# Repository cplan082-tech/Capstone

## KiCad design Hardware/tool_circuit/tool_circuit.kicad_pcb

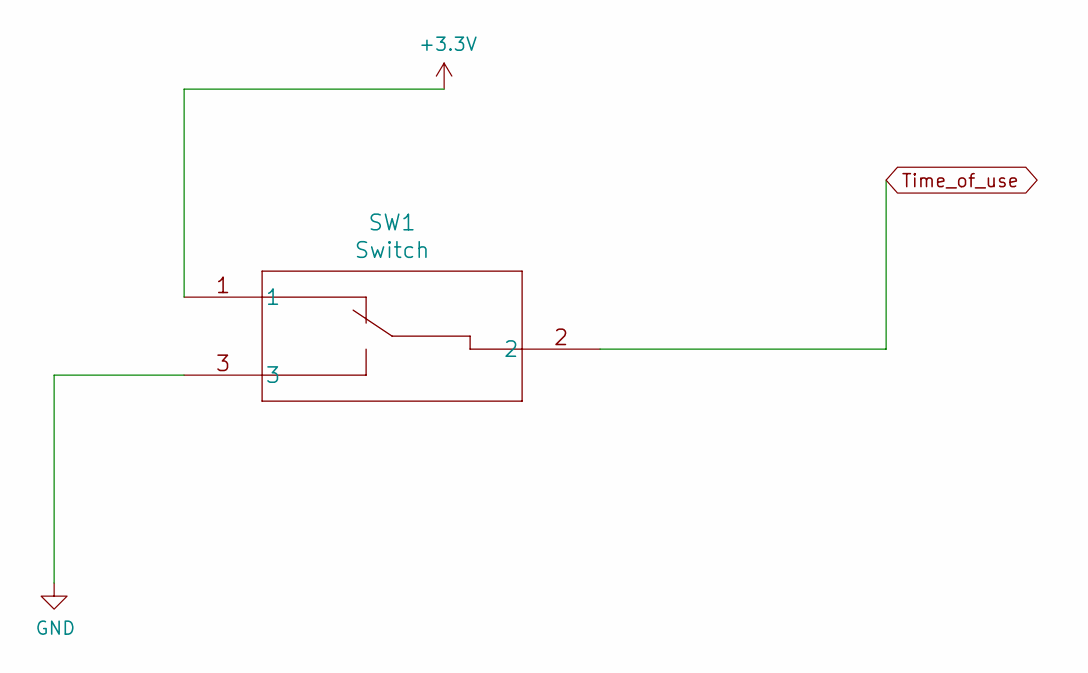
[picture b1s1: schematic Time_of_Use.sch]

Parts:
SW1: Switch; 1825255-1

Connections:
+3V3: SW1.1; also elsewhere on the board
GND: SW1.3; also elsewhere on the board
Time_of_use: SW1.2; also elsewhere on the board

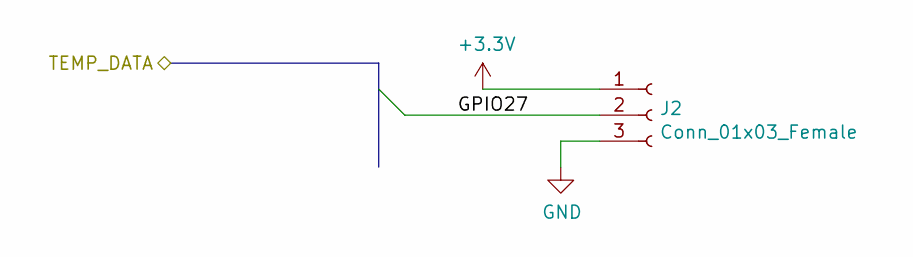
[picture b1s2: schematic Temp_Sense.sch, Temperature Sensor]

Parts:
J2: Conn_01x03_Female; PinHeader_1x03_P2.54mm_Vertical

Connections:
+3V3: J2.1; also elsewhere on the board
GND: J2.3; also elsewhere on the board
GPIO27_GEN2: J2.2; also elsewhere on the board

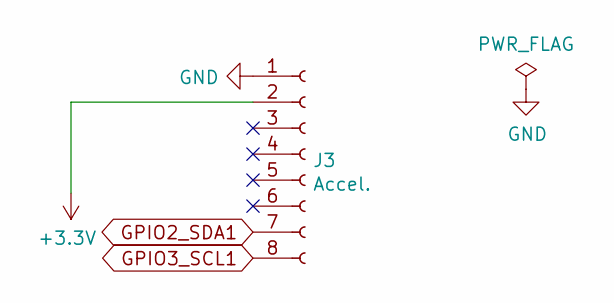
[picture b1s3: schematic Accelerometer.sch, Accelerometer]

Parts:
J3: Accel.; PinHeader_1x08_P2.54mm_Vertical

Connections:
+3V3: J3.2; also elsewhere on the board
GND: J3.1; also elsewhere on the board
GPIO2_SDA1: J3.7; also elsewhere on the board
GPIO3_SCL1: J3.8; also elsewhere on the board

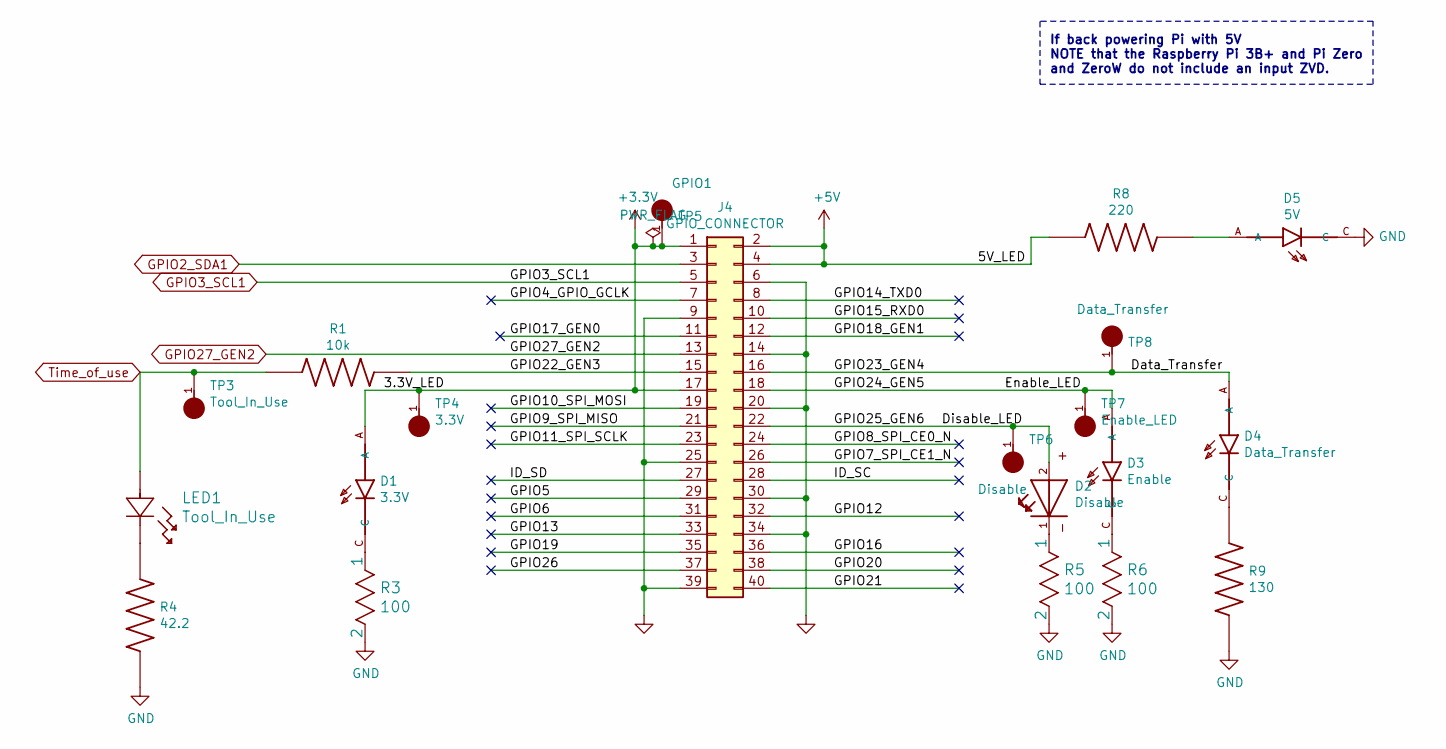
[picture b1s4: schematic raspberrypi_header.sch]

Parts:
D1: 3.3V; LED_WP7113GD
D2: Disable; LED-5MM-ROUND
D3: Enable; LED_WP7113GD
D4: Data_Transfer; LED_WP7113YD
D5: 5V; LED_WP7113GD
J4: GPIO_CONNECTOR; PinSocket_2x20_P2.54mm_Vertical_Centered_Anchor
LED1: Tool_In_Use; 151034BS03000
R1: 10k; RESC3115X60N
R3, R5, R6: 100; RESC3115X60N
R4: 42.2; RESC3116X65N
R8: 220; RESC3216X70N
R9: 130; RESC3116X65N
TP3: Tool_In_Use; HARWIN_S2751-46R
TP4: 3.3V; HARWIN_S2751-46R
TP5: GPIO1; HARWIN_S2751-46R
TP6: Disable; HARWIN_S2751-46R
TP7: Enable_LED; HARWIN_S2751-46R
TP8: Data_Transfer; HARWIN_S2751-46R

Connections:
+3V3: D1.A, J4.1, J4.17, TP4.1, TP5.1; also elsewhere on the board
+5V: J4.2, J4.4, R8.1; also elsewhere on the board
/raspberrypi_header.sch/Data_Transfer: D4.A, J4.16, TP8.1
/raspberrypi_header.sch/Disable_LED: D2.2, J4.22, TP6.1
/raspberrypi_header.sch/Enable_LED: D3.A, J4.18, TP7.1
/raspberrypi_header.sch/GPIO4_GPIO_GCLK: J4.7
/raspberrypi_header.sch/GPIO5: J4.29
/raspberrypi_header.sch/GPIO6: J4.31
/raspberrypi_header.sch/GPIO7_SPI_CE1_N: J4.26
/raspberrypi_header.sch/GPIO8_SPI_CE0_N: J4.24
/raspberrypi_header.sch/GPIO9_SPI_MISO: J4.21
/raspberrypi_header.sch/GPIO10_SPI_MOSI: J4.19
/raspberrypi_header.sch/GPIO11_SPI_SCLK: J4.23
/raspberrypi_header.sch/GPIO12: J4.32
/raspberrypi_header.sch/GPIO13: J4.33
/raspberrypi_header.sch/GPIO14_TXD0: J4.8
/raspberrypi_header.sch/GPIO15_RXD0: J4.10
/raspberrypi_header.sch/GPIO16: J4.36
/raspberrypi_header.sch/GPIO17_GEN0: J4.11
/raspberrypi_header.sch/GPIO18_GEN1: J4.12
/raspberrypi_header.sch/GPIO19: J4.35
/raspberrypi_header.sch/GPIO20: J4.38
/raspberrypi_header.sch/GPIO21: J4.40
/raspberrypi_header.sch/GPIO22_GEN3: J4.15, R1.2
/raspberrypi_header.sch/GPIO26: J4.37
/raspberrypi_header.sch/ID_SC: J4.28
/raspberrypi_header.sch/ID_SD: J4.27
GND: D5.C, J4.6, J4.9, J4.14, J4.20, J4.25, J4.30, J4.34, J4.39, R3.2, R4.2, R5.2, R6.2, R9.2; also elsewhere on the board
GPIO2_SDA1: J4.3; also elsewhere on the board
GPIO3_SCL1: J4.5; also elsewhere on the board
GPIO27_GEN2: J4.13; also elsewhere on the board
unnamed: D1.C, R3.1
unnamed: D2.1, R5.1
unnamed: D3.C, R6.1
unnamed: D4.C, R9.1
unnamed: D5.A, R8.2
unnamed: LED1.1, R4.1
Time_of_use: LED1.2, R1.1, TP3.1; also elsewhere on the board

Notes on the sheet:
If back powering Pi with 5V NOTE that the Raspberry Pi 3B+ and Pi Zero and ZeroW do not include an input ZVD.

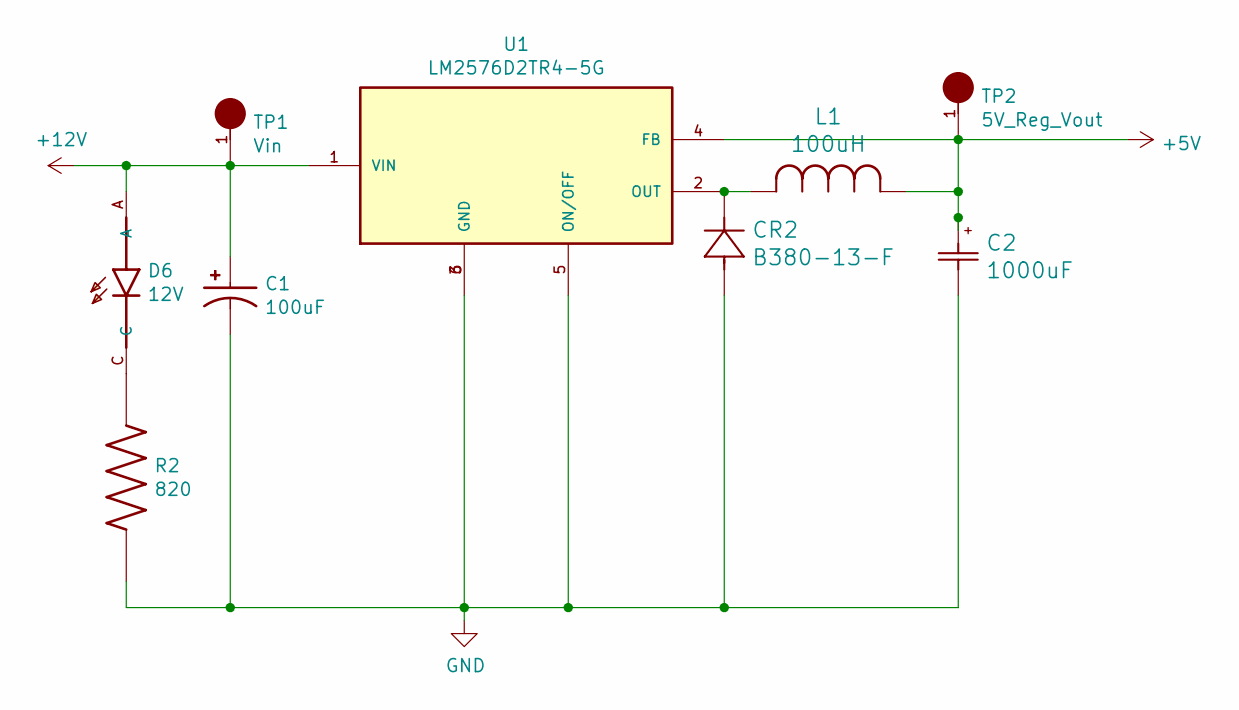
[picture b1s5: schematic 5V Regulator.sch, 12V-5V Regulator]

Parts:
C1: 100uF; CAPPRD500W60D1000H1250; PARTREV 28-FEB-20
C2: 1000uF; URS1E102MHD1TO
CR2: B380-13-F
D6: 12V; LED_WP7113GD
L1: 100uH; IHLP4040DZER101M11
R2: 820; RESC3115X65N
TP1: Vin; HARWIN_S2751-46R
TP2: 5V_Reg_Vout; HARWIN_S2751-46R
U1: LM2576D2TR4-5G; D2PAK-5

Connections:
+5V: C2.1, L1.1, TP2.1, U1.4 (FB); also elsewhere on the board
+12V: C1.P, D6.A, TP1.1, U1.1 (VIN); also elsewhere on the board
GND: C1.N, C2.2, CR2.2, R2.2, U1.3 (GND), U1.5 (ON/OFF), U1.6 (GND); also elsewhere on the board
unnamed: CR2.1, L1.2, U1.2 (OUT)
unnamed: D6.C, R2.1

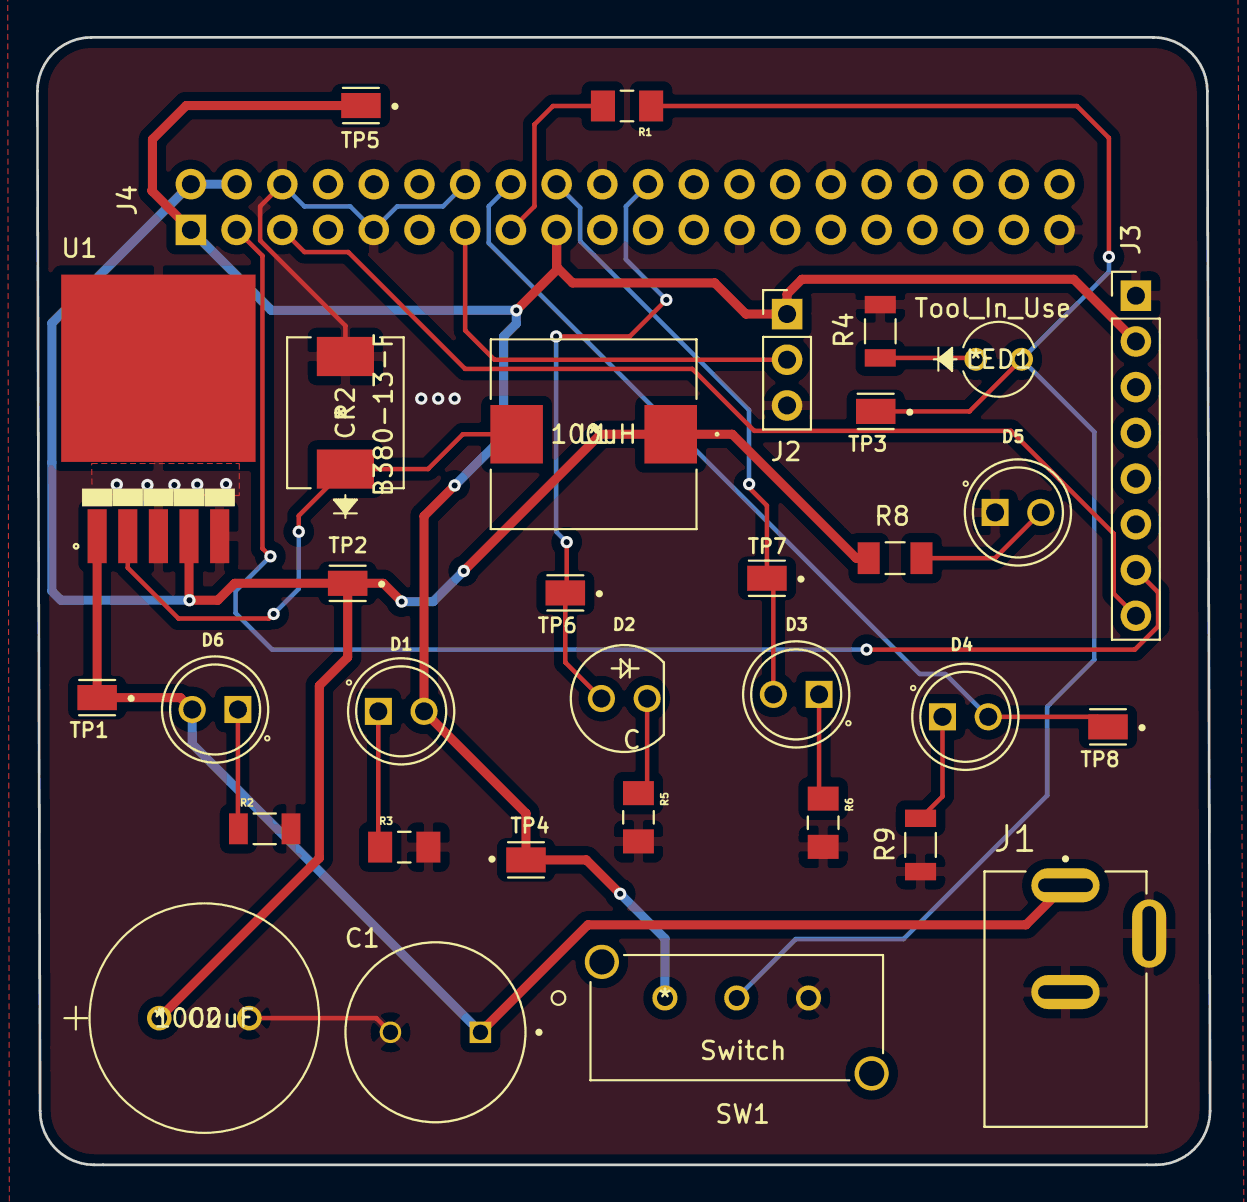
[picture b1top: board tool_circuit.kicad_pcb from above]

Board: 2 copper layers, 65.2 x 62.6 mm, 33 parts (1 on the bottom side), 20 nets.

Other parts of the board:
J1: EJ503A; MPD_EJ503A

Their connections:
+12V: J1.1; also elsewhere on the board
GND: J1.2, J1.3; also elsewhere on the board

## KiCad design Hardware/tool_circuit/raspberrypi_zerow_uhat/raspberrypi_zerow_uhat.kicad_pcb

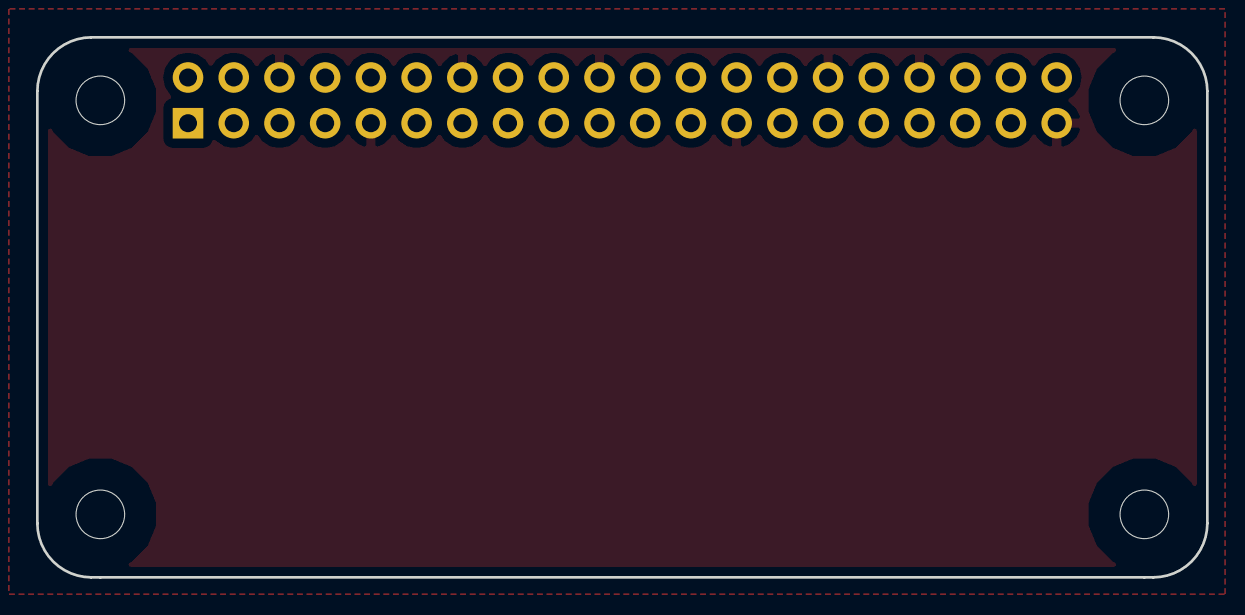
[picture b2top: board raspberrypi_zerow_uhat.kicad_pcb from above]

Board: 2 copper layers, 65.0 x 30.0 mm, 5 parts (1 on the bottom side), 3 nets, no tracks yet.

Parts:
H1, H2, H3, H4: MountingHole; MountingHole_2.7mm_M2.5_uHAT_RPi
J1: GPIO_CONNECTOR; PinSocket_2x20_P2.54mm_Vertical_Centered_Anchor

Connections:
+3V3: J1.1, J1.17
+5V: J1.2, J1.4
GND: J1.6, J1.9, J1.14, J1.20, J1.25, J1.30, J1.34, J1.39

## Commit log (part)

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2021-06-08 Created tool circuit project in kicad
2021-06-08 git test
2021-06-08 updated test.txt
2021-07-08 added digikey library to 'Project_library' folder
2021-07-08 Linked kicad symbols and footprints to project library
2021-07-08 testing digikey library
2021-07-08 tried removing .gitmodules
2021-07-08 Moved .gitmodules back into repo
2021-07-11 komal testing dk library
2021-08-17 test
2021-08-19 Created hierarchy in schematic
2021-08-19 Clive test
2021-08-19 Clive test 2
2021-08-19 conflict test
2021-08-24 temp sensor
2021-08-29 Pi hat
2021-09-08 regulator/other changes
2021-09-13 5v regulator
2021-09-14 Deleted kicad-rpiz-uhat-template folder (was empty) and added file structer for code in SW section
2021-09-14 commmiting test.txt
2021-09-14 Added hub code
2021-09-14 nick's first addition to server
    nick nick teste test
2021-09-14 Edited test.txt
2021-09-14 pi to pi script
2021-09-14 removed test stuff
2021-09-15 Created blank file for tool control code
2021-09-15 Updated hub code
2021-09-15 testing git on pie using SSH
2021-09-16 Added code for temp sensor
2021-09-16 Created Doc Folder. Added tool and Transponder section to Work plan
2021-09-16 Trimmed down original temp_sense script. Added date/time stamp for each data selection. Tupple created with (sensor name,temp, humdity, datetime)
2021-09-16 Created Datasheet folder in Capstone -> Docs
2021-09-16 symbols
2021-09-16 symbols paths updated
2021-09-16 updated symbol paths
2021-09-16 symbolsssss
2021-09-17 updated symbols/footprint paths for today
2021-09-17 Finished first draft of Workplan Doc
2021-09-17 Moved project_proposal doc from google drive to repo. The version of the doc is the post trimed by Komal
2021-09-17 Added a nice2have in hub section of workorder doc
2021-09-17 Created updated system block diagram for project_proposal doc
2021-09-18 Created accelerometer.py script
2021-09-18 Added vib_sense.py script
2021-09-18 Added events to accelerometer.pyscript
2021-09-19 edited proposal doc + started pcb layout
2021-09-19 First draft of time_of_use.py script
2021-09-19 debuging time_of_use.py. Error Rec: 'RuntimeError: Conflicting edge detection already enabled for this GPIO channel'.
2021-09-19 fixed compile bugs
2021-09-19 debuggin debounce bug
2021-09-19 Created 'sensor_pinout' doc
2021-09-21 pcb layout and schematic changes
2021-09-22 'time of use.py' works with capacitor of 10 uF at GPIO
2021-09-22 Base for 'time_of_use.py'
2021-09-22 test: trying to call 'time_of_use.py' from 'tool_control.py'
2021-09-22 updated 'time_of_use.py'
2021-09-22 fixed 'import' bug
2021-09-22 Debugging 'prev_val' bug
2021-09-22 Removed 'Docs' folder
2021-09-22 changed schematic sheet name
2021-09-22 'previous state' bug fix ready for testing
2021-09-23 Added accelerometer to 'tool_control.py' script
2021-09-23 fix for accelerometer integration into 'tool_control.py' script ready for testing
2021-09-23 fix2 for accelerometer integration into 'tool_control.py' script ready for testing
2021-09-23 fix3 for accelerometer integration into 'tool_control.py' script ready for testing
2021-09-23 temp/humidity sense integration into tool_control.py ready for test
2021-09-23 packing data into csv (started)
2021-09-23 Tool Circuit schematic updates
2021-09-24 my scripts added
2021-09-24 edit
2021-09-24 Changed 'tool on LED' to its own GPIO pin and updated 'time_of_use.py' to reflect that
2021-09-24 LED GPIO output setting/reseting bug fix 1 ready for test
2021-09-24 fixed code sequency issue
2021-09-25 Created enable functionality for tool control
2021-09-25 enable function working
2021-09-25 small changes
2021-09-27 schematic revisions
2021-09-28 schematic LEDs + switch
2021-09-28 made some post review changes
2021-10-02 Created enable timer interupt. Ready for testing
2021-10-02 interupt working but exits after first interupt
2021-10-02 Interupt functioning without exiting program when interupt initiated. Fixed by adding global variables in the exception handeler 'enable_timerOut_handler'
2021-10-04 Removed profanity from code
2021-10-04 Removed some of the test code
2021-10-04 Added detection for colisions, freefall and motion to 'tool_control.py'
2021-10-04 Added print statment to print a portrion of the package
2021-10-04 Added time of use to transponder bound package. Read for test 1
2021-10-04 Fixed silly bug
2021-10-04 Fixed bugs relating to packaging of 'time of use'
2021-10-05 Started 'to_csv' functionality
2021-10-05 Created dict_to_csv function. Ready for testing
2021-10-05 Added 'except' portion of 'try and except' block. Generated first test csv file with sensor data
2021-10-05 Created Tool_memory.csv
2021-10-05 Created 'template.csv' file
2021-10-08 wifi scripts added
2021-10-08 Updated
    made adjustements to hub and transponder wifi comms
2021-10-09 Latest revisions to schematic
2021-10-09 Latest schematic revisions
2021-10-20 udpated circuit
2021-10-24 trying to ignor a particular file 'testing_something.txt'
2021-10-24 Removed 'testing_something.txt' from cache on desktop
2021-10-24 trying to ignor 'testing_something.txt.txt'
2021-10-27 schematic updates
2021-10-30 PCB changes
2021-11-01 layout
2021-11-07 Created 'csv_manipulation.py' which contains all functions that do work on csvs. Fujnctions included are 'csv_concat' and 'dict_to_csv' so far
2021-11-07 Refactored 'Tool_control' to use 'csv_manipulation' for writing the sensor data to csv rather than a function defined within itself
2021-11-07 Fixed integration bug in 'Tool_control.py'. Bug due to integrating 'csv_manipulation.py' into program flow
2021-11-07 Updated 'transponder_control.py' and is ready for testing
2021-11-07 Sensor data successfully being moved to memory location and updating csv file there with new data if one already exists. If no csv file is present, a new one is created with new data
2021-11-08 created 'wifi_param_extract' function
2021-11-08 Moved 'wifi_comms.py' to 'test' folder
2021-11-08 minor updates
2021-11-08 'wifi_comms.py' now retrives it's info such as password, IP address for source and destination from a csv just outside the repo
2021-11-08 'wifi_transponder.py' is Clive's new version. Kept Nick's version and called it 'wifi_transponder_nick_version.py'
2021-11-08 Seperated date and time from satetime_stamp and gave them their respective columns
2021-11-08 Move tou.tool_enable(enable) from interupt handeler to main script (tool_conttrol.py). If this is not too slow, configuration will be kept and enable_timerOut_handler will be moved to 'transponder_co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
2021-11-08 Cleaned up 'wifi_transponder.py' to not continuously define all of it's functions. Did this by moving function definitions outside of while loop. Updated while loop to run indefinetly (forever) inste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
2021-11-09 'transponder_control.py' now creates a 'flag.csv' once before entering the while loop. This is just for testing hte flag portion of 'wifi_transponder.py'
2021-11-09 small test
2021-11-09 fixed syntax issue
2021-11-09 pcb revisions
2021-11-10 AWS Block Diagram :)
2021-11-11 gerber files
2021-11-11 Updated Gerbers
2021-11-11 Added Alert functionality, right now there is a variable called Alert which is currently set to False. Set to True if the tool is stolen.
2021-11-15 Added blank 'wifi_params.csv' file in first level of Capstone repo
2021-11-16 Preped 'tool_control.py' for demo
2021-11-16 Added to 'tool_control.py' if statement that checkes if time_of_use accumulator has data in it before transfering data to csv and reseting accumulator
2021-11-16 Fixed minor bug from last commit, accumulator does not reset like it should
2021-11-16 In 'tool_control.py' resets 'time_of_use' variable once recoded
2021-11-16 Updated 'wifi_transponder.py' to fix flag bug
2021-11-16 not sure what happened here
2021-11-16 Commented out Temperature Sensor in 'tool_control.py'
2021-11-17 tool_control.py - Tool can now operate for 10 seconds before it needs to receive a new 'flag.csv' wifi_transponder.py - Commented out line that deletes local copy of 'flag.csv'
2021-11-17 tool_control.py - not sure lol transponder_control.py - added enable timer
2021-11-17 quicky fixy
2021-11-17 quick bug fix
2021-11-17 transponder_control.py - Integration bug - code worked when 'enable_timer_val.csv' is placed in tooldump folderfor first time but crashes second time
2021-11-18 time of use function
2021-11-23 Updated Hub code + Update timer stuff
2021-11-23 Timer stuff
2021-11-25 added my latest Wifi script
2021-11-26 quick commit
2021-11-26 kjhndklhsdlkh
2021-11-26 adjusted script
2021-11-26 more edits
2021-11-26 mroe changes
2021-11-26 more changes
2021-11-26 ghgeh
2021-11-26 quick debug
2021-11-26 sdfmgkjsd
2021-11-26 nfhshdg
2021-11-26 Data being transfered from tool to hub succesfuly. Enable timer in transponder can be updated from teh hub
2021-11-30 added tocken to repo
2021-12-01 added aws
2021-12-01 teesting
2021-12-01 change
2021-12-01 edits to script
2021-12-02 added 'setup_aws.sh' Software/AWS
2021-12-02 updated 'tool_control.py' to control the enable and disable LEDs
2021-12-02 Changed pin assingment in 'tool_control.py' and 'time_of_use.py' to match the pinout of the PCB
2021-12-02 Changed ips to my pis
2021-12-02 Initialised LED GPIO pins in 'tool_control.py' as outputs
2021-12-02 Changed datatransfer pin from GPIO 23 to GPIO 4 in 'tool_control.py'. This LED will be used for indicating when the tool is in use
2021-12-02 Changed path from home/Tool/... to home/pi/...
2021-12-03 Fixed LED bugs (enable/disable)
2021-12-03 Added comments in 'transponder_control'
2021-12-03 added comments to 'transponder_control.py'
2021-12-03 Cleand code for 'tool_control.py', 'time_of_use.py' and 'transponder_control.py'
2021-12-03 script setup
2021-12-03 changed trasponder ip to proper one
2021-12-03 Updated 'wifi_comms' script to use enable switch
2021-12-03 Fixing deleting Tool_Memory.csv bug in wifi script
2021-12-03 hfkjafk
2021-12-03 added clive's hub pi's IP to wifi_comms
2021-12-03 changed credentials in wifi_commms to match Clive's
2021-12-03 Updated timer.csv path in transponder_control
2021-12-03 bug fix (flag path in wifi comms)
2021-12-03 sdkljfgasd
2021-12-03 Updated transponder control to delete flag only if it exists
2021-12-03 Attempt at csv_manip workaround
2021-12-03 revert previous change
2021-12-03 desperation
2021-12-03 almost ther
2021-12-03 dkjnowf
2021-12-03 Send() function in wifi_comms updated to correct file i.e. 'Tool_Memory_acumulator.csv'
2021-12-03 quick add on to last commit
2021-12-03 fior testing
2021-12-03 Updated 'csv_manipulator.py' to create tempcsv if file outputname already exists
2021-12-03 quicj fix
2021-12-03 push
2021-12-03 'csv_concat' Function not working anymore
2021-12-03 preparing to look at working version of csv_manip
2021-12-03 csv_concat bug fixedgit statusgit statusgit statusgit statusgit statusgit statusgit statusgit statusgit statusgit statusgit statusgit statusgit statusgit statusgit status!
2021-12-03 added slashes where needed in wifi_comms
2021-12-03 djkosd
2021-12-03 quick fix
2021-12-03 rest wifi_coms to test old working setup
2021-12-04 Transponder and tool are capable of working together now
2021-12-04 updated path for when incoming sensor data gets stored in the hub
2021-12-04 Sensor data will not send to the hub
2021-12-04 added hit marker
2021-12-04 See if change breaks receive/send functionality
2021-12-04 Enabled timer, flag, send and receive
2021-12-04 Tool Transponder and Hub are working. Just need to test whole chain now
2021-12-05 added PCB schematic PDF called 'pi connector pinout'
2021-12-05 forgot to add PDF
2021-12-05 Added old pcb schematic
2021-12-05 ssh credentials
2021-12-05 changed IPs in wifi_transponder_nick
2021-12-05 pulling
2021-12-05 script changes
2021-12-05 updated tool_memory.csv format
2021-12-05 updated test csv file to have 'holder rows'
2021-12-05 removed seconds from datime
2021-12-05 Updated Misc_Functions.py to clean time_of_use column
2021-12-05 Recreated Memory folder in wifi_comms folder
2021-12-05 This is a working copy
2021-12-05 updated sleep timers in wifi_comms script
2021-12-06 Added condition for checking if any 'holder' values are in the sensor data
2021-12-06 Updated path for timer file
2021-12-06 Updated tool timer to 1 min 30 sec

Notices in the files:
Hardware/tool_circuit/raspberrypi_zerow_uhat/raspberrypi_zerow_uhat.kicad_pcb:
This PCB design is licensed under MIT Open Source License.
parts and their libraries:
Copyright 2021 Accelerated Designs. All rights reserved.
